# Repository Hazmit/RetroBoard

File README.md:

RetroBoard
==========

Example Joystick PCB Design

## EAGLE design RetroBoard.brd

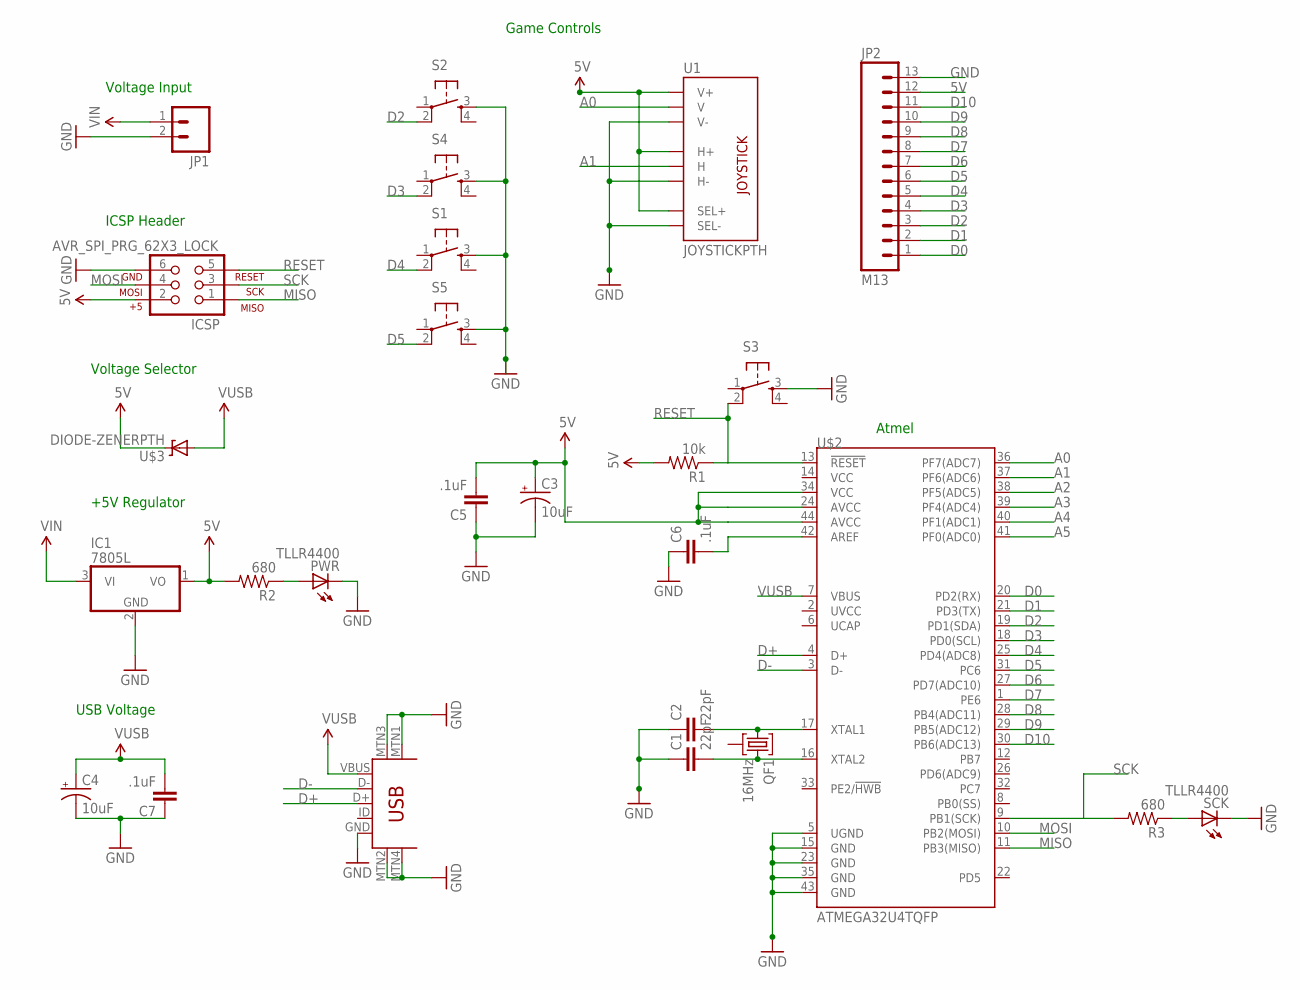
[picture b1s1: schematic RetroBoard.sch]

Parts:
C1, C2: 22pF; CAP-PTH-SMALLEZ
C3, C4: 10uF; CPOL-RADIAL-1000UF-25V
C5, C6, C7: .1uF; CAP-PTH-SMALLEZ
IC1: 7805L; TO92
ICSP: AVR_SPI_PRG_62X3_LOCK; 2X3_LOCK
JP1: M02LOCK; 1X02_LOCK
JP2: M13; 1X13
PWR: TLLR4400; LED3MM
QF1: 16MHz; HC49U
R1: 10k; AXIAL-0.3
R2, R3: 680; AXIAL-0.3
S1: TAC_SWITCHSMD; TACTILE_SWITCH_SMD
S2, S3, S4, S5: TAC_SWITCHPTH; TACTILE-PTH
SCK: TLLR4400; LED3MM
U1: JOYSTICKPTH; JOYSTICK
U$2: ATMEGA32U4TQFP; SPARKFUN-DIGITALIC_TQFP44
U$3: DIODE-ZENERPTH; DIODE-ZENER
USB: USB-MINIB-5PIN; USB-MINIB

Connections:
5V: C3.1 (+), C5.2, IC1.1 (VO), ICSP.2, JP2.12, R1.P$2 (2), R2.P$2 (2), U1.B1A (SEL+), U1.H1 (H+), U1.V1 (V+), U$2.24 (AVCC), U$2.34 (VCC), U$2.44 (AVCC), U$3.P$1 (C)
A0: U1.V2 (V), U$2.36 (PF7(ADC7))
A1: U1.H2 (H), U$2.37 (PF6(ADC6))
A2: U$2.38 (PF5(ADC5))
A3: U$2.39 (PF4(ADC4))
A4: U$2.40 (PF1(ADC1))
A5: U$2.41 (PF0(ADC0))
D0: JP2.1, U$2.20 (PD2(RX))
D1: JP2.2, U$2.21 (PD3(TX))
D2: JP2.3, S2.2, U$2.19 (PD1(SDA))
D3: JP2.4, S4.2, U$2.18 (PD0(SCL))
D4: JP2.5, S1.2, U$2.25 (PD4(ADC8))
D5: JP2.6, S5.2, U$2.31 (PC6)
D6: JP2.7, U$2.27 (PD7(ADC10))
D7: JP2.8, U$2.1 (PE6)
D8: JP2.9, U$2.28 (PB4(ADC11))
D9: JP2.10, U$2.29 (PB5(ADC12))
D10: JP2.11, U$2.30 (PB6(ADC13))
D+: U$2.4 (D+), USB.D+
D-: U$2.3 (D-), USB.D-
GND: C1.1, C2.1, C3.2 (-), C4.2 (-), C5.1, C6.1, C7.1, IC1.2 (GND), ICSP.6, JP1.2, JP2.13, PWR.K (C), S1.3, S2.3, S3.3, S4.3, S5.3, SCK.K (C), U1.B2A (SEL-), U1.H3 (H-), U1.V3 (V-), U$2.5 (UGND), U$2.15 (GND), U$2.23 (GND), U$2.35 (GND), U$2.43 (GND), USB.GND, USB.MTN1 (MTN2), USB.MTN2 (MTN3), USB.MTN3 (MTN1), USB.MTN4
MISO: ICSP.1, U$2.11 (PB3(MISO))
MOSI: ICSP.4, U$2.10 (PB2(MOSI))
unnamed: PWR.A, R2.P$1 (1)
unnamed: C2.2, QF1.1, U$2.17 (XTAL1)
unnamed: C1.2, QF1.3, U$2.16 (XTAL2)
unnamed: C6.2, U$2.42 (AREF)
unnamed: R3.P$1 (1), SCK.A
RESET: ICSP.5, R1.P$1 (1), S3.2, U$2.13 (!RESET)
SCK: ICSP.3, R3.P$2 (2), U$2.9 (PB1(SCK))
VIN: C4.1 (+), C7.2, IC1.3 (VI), JP1.1, U$3.P$2 (A), USB.VBUS
VUSB: U$2.7 (VBUS)

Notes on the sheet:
ICSP Header
Game Controls
+5V Regulator
Voltage Input
Voltage Selector
USB Voltage
Atmel

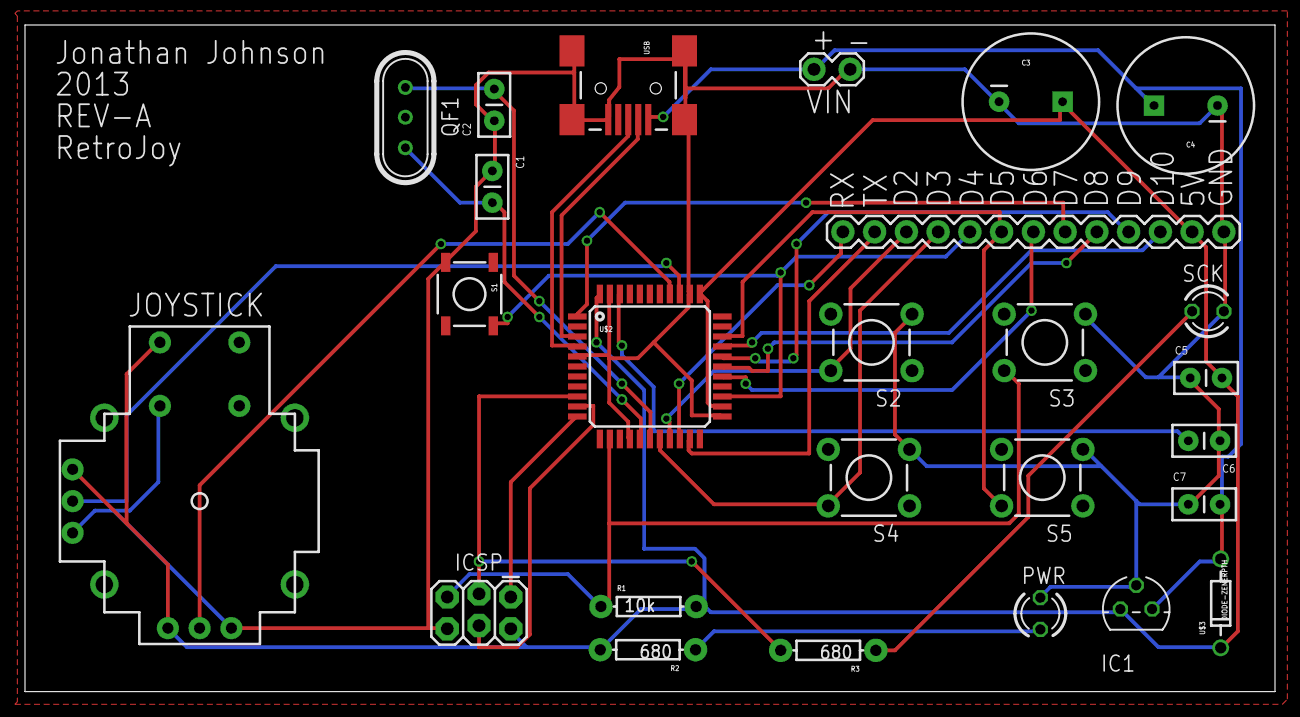
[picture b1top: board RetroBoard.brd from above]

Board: 2 copper layers, 100.0 x 53.3 mm, 26 parts (0 on the bottom side), 27 nets.

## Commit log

2013-10-17 Adding initial board files from Eagle CAD
2013-10-17 Adding screen shot PDF images of board and schematic

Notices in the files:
parts and their libraries:
SparkFun-DigitalIC: Licensing: CC v3.0 Share-Alike You are welcome to use this library for commercial purposes.
